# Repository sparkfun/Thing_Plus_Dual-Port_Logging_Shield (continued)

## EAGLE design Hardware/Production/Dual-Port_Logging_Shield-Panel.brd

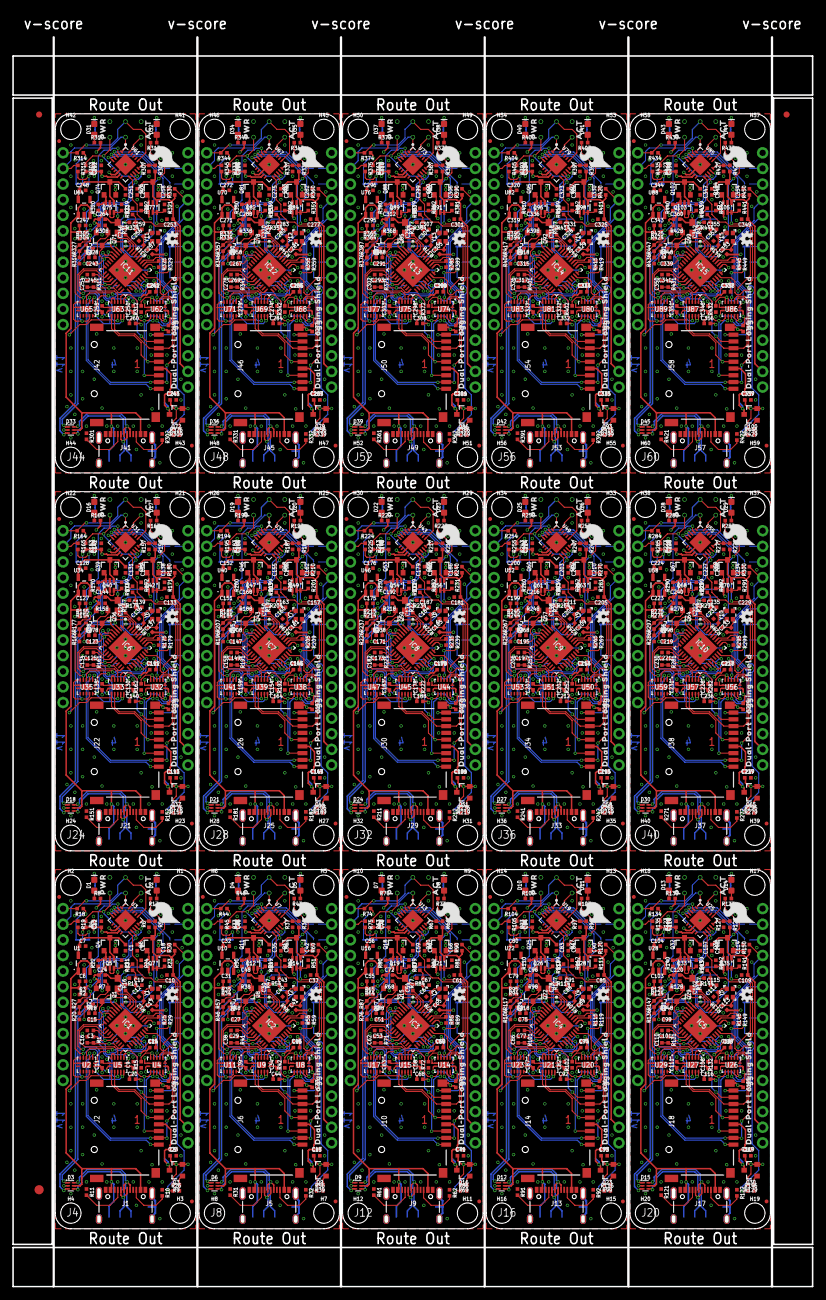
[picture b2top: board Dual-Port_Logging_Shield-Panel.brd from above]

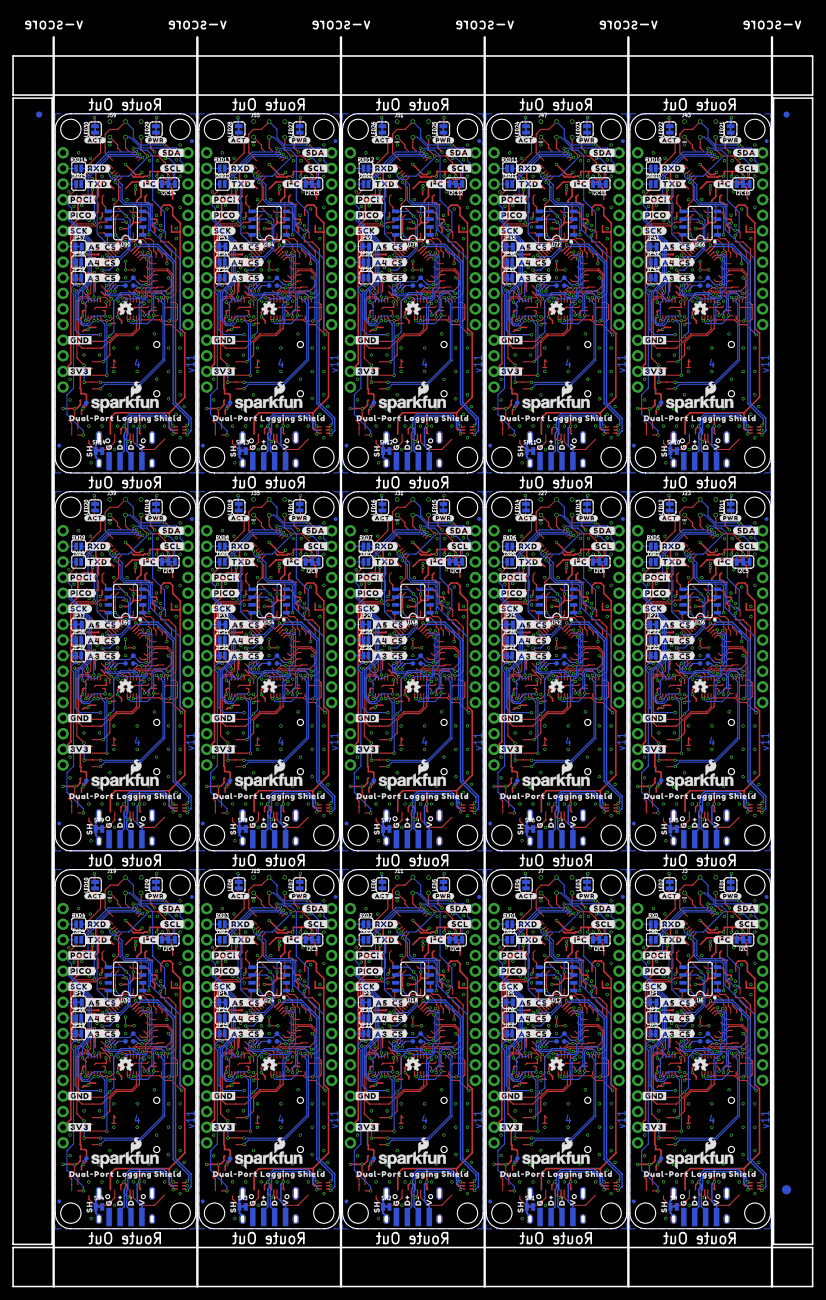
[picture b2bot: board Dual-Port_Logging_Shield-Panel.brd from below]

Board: 4 copper layers, 130.0 x 203.2 mm, 1896 parts (618 on the bottom side), 1095 nets.

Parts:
C1, C2, C5, C8, C9, C11, C13, C14, C16, C19, C25, C26, C28, C33, C34, C35, C36, C38, C39, C43, C49, C50, C52, C57, C58, C59, C60, C62, C63, C67, C73, C74, C76, C81, C82, C83, C84, C86, C87, C91, C97, C98, C100, C105, C106, C107, C108, C110, C111, C115, C121, C122, C124, C129, C130, C131, C132, C134, C135, C139, C145, C146, C148, C153, C154, C155, C156, C158, C159, C163, C169, C170, C172, C177, C178, C179, C180, C182, C183, C187, C193, C194, C196, C201, C202, C203, C204, C206, C207, C211, C217, C218, C220, C225, C226, C227, C228, C230, C231, C235, C241, C242, C244, C249, C250, C251, C252, C254, C255, C259, C265, C266, C268, C273, C274, C275, C276, C278, C279, C283, C289, C290, C292, C297, C298, C299, C300, C302, C303, C307, C313, C314, C316, C321, C322, C323, C324, C326, C327, C331, C337, C338, C340, C345, C346, C347, C348, C350, C351, C355: 0.1uF; 0402-TIGHT
C3, C4, C6, C7, C10, C15, C18, C27, C29, C30, C31, C32, C37, C42, C51, C53, C54, C55, C56, C61, C66, C75, C77, C78, C79, C80, C85, C90, C99, C101, C102, C103, C104, C109, C114, C123, C125, C126, C127, C128, C133, C138, C147, C149, C150, C151, C152, C157, C162, C171, C173, C174, C175, C176, C181, C186, C195, C197, C198, C199, C200, C205, C210, C219, C221, C222, C223, C224, C229, C234, C243, C245, C246, C247, C248, C253, C258, C267, C269, C270, C271, C272, C277, C282, C291, C293, C294, C295, C296, C301, C306, C315, C317, C318, C319, C320, C325, C330, C339, C341, C342, C343, C344, C349, C354: 2.2uF; 0402-TIGHT
C12, C17, C40, C41, C64, C65, C88, C89, C112, C113, C136, C137, C160, C161, C184, C185, C208, C209, C232, C233, C256, C257, C280, C281, C304, C305, C328, C329, C352, C353: 12pF; 0402-TIGHT
C20, C21, C22, C23, C24, C44, C45, C46, C47, C48, C68, C69, C70, C71, C72, C92, C93, C94, C95, C96, C116, C117, C118, C119, C120, C140, C141, C142, C143, C144, C164, C165, C166, C167, C168, C188, C189, C190, C191, C192, C212, C213, C214, C215, C216, C236, C237, C238, C239, C240, C260, C261, C262, C263, C264, C284, C285, C286, C287, C288, C308, C309, C310, C311, C312, C332, C333, C334, C335, C336, C356, C357, C358, C359, C360: 10uF; 0402-TIGHT
D1, D4, D7, D10, D13, D16, D19, D22, D25, D28, D31, D34, D37, D40, D43: RED; LED-0603
D2, D5, D8, D11, D14, D17, D20, D23, D26, D29, D32, D35, D38, D41, D44: Yellow; LED-0603
D3, D6, D9, D12, D15, D18, D21, D24, D27, D30, D33, D36, D39, D42, D45: PRTR5V0U2F; SOT886
E$1, E$2, E$3, E$4: FIDUCIAL-1X2
E$5, E$6: FIDUCIAL-1.5X3
FD1, FD2, FD3, FD4, FD5, FD6, FD7, FD8, FD9, FD10, FD11, FD12, FD13, FD14, FD15, FD16, FD17, FD18, FD19, FD20, FD21, FD22, FD23, FD24, FD25, FD26, FD27, FD28, FD29, FD30, FD31, FD32, FD33, FD34, FD35, FD36, FD37, FD38, FD39, FD40, FD41, FD42, FD43, FD44, FD45, FD46, FD47, FD48, FD49, FD50, FD51, FD52, FD53, FD54, FD55, FD56, FD57, FD58, FD59, FD60: FIDUCIALUFIDUCIAL; FIDUCIAL-MICRO
GPIO1, GPIO2, GPIO3, GPIO4, GPIO5, GPIO6, GPIO7, GPIO8, GPIO9, GPIO10, GPIO11, GPIO12, GPIO13, GPIO14, GPIO15: TEST-POINT3; PAD.03X.03
H1, H2, H3, H4, H5, H6, H7, H8, H9, H10, H11, H12, H13, H14, H15, H16, H17, H18, H19, H20, H21, H22, H23, H24, H25, H26, H27, H28, H29, H30, H31, H32, H33, H34, H35, H36, H37, H38, H39, H40, H41, H42, H43, H44, H45, H46, H47, H48, H49, H50, H51, H52, H53, H54, H55, H56, H57, H58, H59, H60: STAND-OFF
I2C, I2C1, I2C2, I2C3, I2C4, I2C5, I2C6, I2C7, I2C8, I2C9, I2C10, I2C11, I2C12, I2C13, I2C14: JUMPER-SMT_3_2-NC_TRACE_SILK; SMT-JUMPER_3_2-NC_TRACE_SILK
IC1, IC2, IC3, IC4, IC5, IC6, IC7, IC8, IC9, IC10, IC11, IC12, IC13, IC14, IC15: USB224X_2241_V04; 36-QFN
J1, J5, J9, J13, J17, J21, J25, J29, J33, J37, J41, J45, J49, J53, J57: USB-C-16P_4LAYER-PADS
J2, J6, J10, J14, J18, J22, J26, J30, J34, J38, J42, J46, J50, J54, J58: MICRO-SD-PUSH-PUSH-EXT-PIN; MICROSD-EXTERNALPIN
J3, J7, J11, J15, J19, J23, J27, J31, J35, J39, J43, J47, J51, J55, J59: AVR_SPI_PROG_3X2TESTPOINTS; 2X3_TEST_POINTS
J4, J8, J12, J16, J20, J24, J28, J32, J36, J40, J44, J48, J52, J56, J60: THING_PLUS
JP1, JP5, JP9, JP13, JP17, JP21, JP25, JP29, JP33, JP37, JP41, JP45, JP49, JP53, JP57: JUMPER-SMT_2_NC_TRACE_SILK; SMT-JUMPER_2_NC_TRACE_SILK
JP2, JP3, JP6, JP7, JP10, JP11, JP14, JP15, JP18, JP19, JP22, JP23, JP26, JP27, JP30, JP31, JP34, JP35, JP38, JP39, JP42, JP43, JP46, JP47, JP50, JP51, JP54, JP55, JP58, JP59: JUMPER-SMT_2_NO_SILK; SMT-JUMPER_2_NO_SILK
JP4, JP8, JP12, JP16, JP20, JP24, JP28, JP32, JP36, JP40, JP44, JP48, JP52, JP56, JP60: USB_SOLDER_PADS; USB-SOLDER-PADS
LED1, LED2, LED3, LED4, LED5, LED6, LED7, LED8, LED9, LED10, LED11, LED12, LED13, LED14, LED15, LED16, LED17, LED18, LED19, LED20, LED21, LED22, LED23, LED24, LED25, LED26, LED27, LED28, LED29, LED30: JUMPER-SMT_2_NC_TRACE_SILK; SMT-JUMPER_2_NC_TRACE_SILK
LOGO1, LOGO2, LOGO3, LOGO6, LOGO9, LOGO10, LOGO13, LOGO14, LOGO17, LOGO18, LOGO21, LOGO22, LOGO25, LOGO26, LOGO29, LOGO30, LOGO33, LOGO34, LOGO37, LOGO38, LOGO41, LOGO42, LOGO45, LOGO46, LOGO49, LOGO50, LOGO53, LOGO54, LOGO57, LOGO58: OSHW-LOGOMINI; OSHW-LOGO-MINI
LOGO4, LOGO7, LOGO11, LOGO15, LOGO19, LOGO23, LOGO27, LOGO31, LOGO35, LOGO39, LOGO43, LOGO47, LOGO51, LOGO55, LOGO59: SFE_LOGO_FLAME.2_INCH; SFE_LOGO_FLAME_.2
LOGO5, LOGO8, LOGO12, LOGO16, LOGO20, LOGO24, LOGO28, LOGO32, LOGO36, LOGO40, LOGO44, LOGO48, LOGO52, LOGO56, LOGO60: SFE_LOGO_NAME_FLAME.1_INCH; SFE_LOGO_NAME_FLAME_.1
MICROSD_VCC, MICROSD_VCC1, MICROSD_VCC2, MICROSD_VCC3, MICROSD_VCC4, MICROSD_VCC5, MICROSD_VCC6, MICROSD_VCC7, MICROSD_VCC8, MICROSD_VCC9, MICROSD_VCC10, MICROSD_VCC11, MICROSD_VCC12, MICROSD_VCC13, MICROSD_VCC14: TEST-POINT3; PAD.03X.03
Q1, Q3, Q4, Q6, Q8, Q9, Q11, Q13, Q15, Q16, Q18, Q20, Q22, Q23, Q25, Q27, Q29, Q30, Q32, Q34, Q36, Q37, Q39, Q41, Q43, Q44, Q46, Q48, Q50, Q51, Q53, Q55, Q57, Q58, Q60, Q62, Q64, Q65, Q67, Q69, Q71, Q72, Q74, Q76, Q78, Q79, Q81, Q83, Q85, Q86, Q88, Q90, Q92, Q93, Q95, Q97, Q99, Q100, Q102, Q104: 20V/4.2A/52mΩ/1.4W; SOT23-3
Q2, Q10, Q17, Q24, Q31, Q38, Q45, Q52, Q59, Q66, Q73, Q80, Q87, Q94, Q101: 20V/0.2A/8MHz/1.2Ω/1Vth; SOT-416FL
Q5, Q7, Q12, Q14, Q19, Q21, Q26, Q28, Q33, Q35, Q40, Q42, Q47, Q49, Q54, Q56, Q61, Q63, Q68, Q70, Q75, Q77, Q82, Q84, Q89, Q91, Q96, Q98, Q103, Q105: SOT363_PHILIPS
R1, R5, R6, R7, R9, R15, R20, R21, R23, R36, R37, R38, R39, R41, R42, R46, R49, R51, R66, R67, R68, R69, R71, R72, R76, R79, R81, R96, R97, R98, R99, R101, R102, R106, R109, R111, R126, R127, R128, R129, R131, R132, R136, R139, R141, R156, R157, R158, R159, R161, R162, R166, R169, R171, R186, R187, R188, R189, R191, R192, R196, R199, R201, R216, R217, R218, R219, R221, R222, R226, R229, R231, R246, R247, R248, R249, R251, R252, R256, R259, R261, R276, R277, R278, R279, R281, R282, R286, R289, R291, R306, R307, R308, R309, R311, R312, R316, R319, R321, R336, R337, R338, R339, R341, R342, R346, R349, R351, R366, R367, R368, R369, R371, R372, R376, R379, R381, R396, R397, R398, R399, R401, R402, R406, R409, R411, R426, R427, R428, R429, R431, R432, R436, R439, R441: 100k; 0402-TIGHT
R2, R3, R4, R13, R14, R25, R29, R30, R33, R34, R35, R53, R54, R55, R59, R60, R63, R64, R65, R83, R84, R85, R89, R90, R93, R94, R95, R113, R114, R115, R119, R120, R123, R124, R125, R143, R144, R145, R149, R150, R153, R154, R155, R173, R174, R175, R179, R180, R183, R184, R185, R203, R204, R205, R209, R210, R213, R214, R215, R233, R234, R235, R239, R240, R243, R244, R245, R263, R264, R265, R269, R270, R273, R274, R275, R293, R294, R295, R299, R300, R303, R304, R305, R323, R324, R325, R329, R330, R333, R334, R335, R353, R354, R355, R359, R360, R363, R364, R365, R383, R384, R385, R389, R390, R393, R394, R395, R413, R414, R415, R419, R420, R423, R424, R425, R443, R444, R445, R449, R450: 10k; 0402-TIGHT
R8, R17, R40, R43, R70, R73, R100, R103, R130, R133, R160, R163, R190, R193, R220, R223, R250, R253, R280, R283, R310, R313, R340, R343, R370, R373, R400, R403, R430, R433: 1k; 0402-TIGHT
R10, R11, R31, R32, R61, R62, R91, R92, R121, R122, R151, R152, R181, R182, R211, R212, R241, R242, R271, R272, R301, R302, R331, R332, R361, R362, R391, R392, R421, R422: 5.1k; 0402-TIGHT
R12, R22, R24, R48, R50, R52, R78, R80, R82, R108, R110, R112, R138, R140, R142, R168, R170, R172, R198, R200, R202, R228, R230, R232, R258, R260, R262, R288, R290, R292, R318, R320, R322, R348, R350, R352, R378, R380, R382, R408, R410, R412, R438, R440, R442: 1M; 0402-TIGHT
R16, R47, R77, R107, R137, R167, R197, R227, R257, R287, R317, R347, R377, R407, R437: 12k; 0603
R18, R19, R44, R45, R74, R75, R104, R105, R134, R135, R164, R165, R194, R195, R224, R225, R254, R255, R284, R285, R314, R315, R344, R345, R374, R375, R404, R405, R434, R435: 2.2k; 0402-TIGHT
R26, R27, R28, R56, R57, R58, R86, R87, R88, R116, R117, R118, R146, R147, R148, R176, R177, R178, R206, R207, R208, R236, R237, R238, R266, R267, R268, R296, R297, R298, R326, R327, R328, R356, R357, R358, R386, R387, R388, R416, R417, R418, R446, R447, R448: 100; 0402-TIGHT
RXD, RXD1, RXD2, RXD3, RXD4, RXD5, RXD6, RXD7, RXD8, RXD9, RXD10, RXD11, RXD12, RXD13, RXD14: JUMPER-SMT_2_NO_SILK; SMT-JUMPER_2_NO_SILK
SDIO_!RESET!, SDIO_!RESET!1, SDIO_!RESET!2, SDIO_!RESET!3, SDIO_!RESET!4, SDIO_!RESET!5, SDIO_!RESET!6, SDIO_!RESET!7, SDIO_!RESET!8, SDIO_!RESET!9, SDIO_!RESET!10, SDIO_!RESET!11, SDIO_!RESET!12, SDIO_!RESET!13, SDIO_!RESET!14: TEST-POINT3; PAD.03X.03
SDIO_VDD, SDIO_VDD1, SDIO_VDD2, SDIO_VDD3, SDIO_VDD4, SDIO_VDD5, SDIO_VDD6, SDIO_VDD7, SDIO_VDD8, SDIO_VDD9, SDIO_VDD10, SDIO_VDD11, SDIO_VDD12, SDIO_VDD13, SDIO_VDD14: TEST-POINT3; PAD.03X.03
SH, SH1, SH2, SH3, SH4, SH5, SH6, SH7, SH8, SH9, SH10, SH11, SH12, SH13, SH14: JUMPER-SMT_2_NC_TRACE_NO-SILK; SMT-JUMPER_2_NC_TRACE_NO-SILK
TXD, TXD1, TXD2, TXD3, TXD4, TXD5, TXD6, TXD7, TXD8, TXD9, TXD10, TXD11, TXD12, TXD13, TXD14: JUMPER-SMT_2_NO_SILK; SMT-JUMPER_2_NO_SILK
U1, U10, U16, U22, U28, U34, U40, U46, U52, U58, U64, U70, U76, U82, U88: 3.3V; SOT23-5
U2, U4, U5, U8, U9, U11, U14, U15, U17, U20, U21, U23, U26, U27, U29, U32, U33, U35, U38, U39, U41, U44, U45, U47, U50, U51, U53, U56, U57, U59, U62, U63, U65, U68, U69, U71, U74, U75, U77, U80, U81, U83, U86, U87, U89: 74HC4066_QUAD_BILATERAL_SWITCH_QFN; 14-QFN
U3, U7, U13, U19, U25, U31, U37, U43, U49, U55, U61, U67, U73, U79, U85: ATTINY841-ARDUINO_QFN20M1; QFN20_20M1
U6, U12, U18, U24, U30, U36, U42, U48, U54, U60, U66, U72, U78, U84, U90: 24C04; SO08
U$1, U$32, U$56, U$80, U$104, U$128, U$152, U$176, U$200, U$224, U$248, U$272, U$296, U$320, U$344: #SDA#0
U$2, U$33, U$57, U$81, U$105, U$129, U$153, U$177, U$201, U$225, U$249, U$273, U$297, U$321, U$345: #SCL#1
U$3, U$36, U$60, U$84, U$108, U$132, U$156, U$180, U$204, U$228, U$252, U$276, U$300, U$324, U$348: #POCI#0
U$4, U$37, U$61, U$85, U$109, U$133, U$157, U$181, U$205, U$229, U$253, U$277, U$301, U$325, U$349: #PICO#1
U$5, U$38, U$62, U$86, U$110, U$134, U$158, U$182, U$206, U$230, U$254, U$278, U$302, U$326, U$350: #SCK#2
U$6, U$14, U$30, U$31, U$54, U$55, U$78, U$79, U$102, U$103, U$126, U$127, U$150, U$151, U$174, U$175, U$198, U$199, U$222, U$223, U$246, U$247, U$270, U$271, U$294, U$295, U$318, U$319, U$342, U$343: DUAL#PORT_LOGGING_SHIELD0
U$7, U$42, U$66, U$90, U$114, U$138, U$162, U$186, U$210, U$234, U$258, U$282, U$306, U$330, U$354: #GND#0
U$8, U$43, U$67, U$91, U$115, U$139, U$163, U$187, U$211, U$235, U$259, U$283, U$307, U$331, U$355: #3V3#1
U$9, U$34, U$58, U$82, U$106, U$130, U$154, U$178, U$202, U$226, U$250, U$274, U$298, U$322, U$346: #RXD#0
U$10, U$35, U$59, U$83, U$107, U$131, U$155, U$179, U$203, U$227, U$251, U$275, U$299, U$323, U$347: #TXD#1
U$11, U$24, U$49, U$73, U$97, U$121, U$145, U$169, U$193, U$217, U$241, U$265, U$289, U$313, U$337: PWR0
U$12, U$26, U$50, U$74, U$98, U$122, U$146, U$170, U$194, U$218, U$242, U$266, U$290, U$314, U$338: ACT0
U$13, U$27, U$51, U$75, U$99, U$123, U$147, U$171, U$195, U$219, U$243, U$267, U$291, U$315, U$339: #I�C#0
U$15, U$28, U$52, U$76, U$100, U$124, U$148, U$172, U$196, U$220, U$244, U$268, U$292, U$316, U$340: #PWR#0
U$16, U$29, U$53, U$77, U$101, U$125, U$149, U$173, U$197, U$221, U$245, U$269, U$293, U$317, U$341: #ACT#0
U$17, U$39, U$63, U$87, U$111, U$135, U$159, U$183, U$207, U$231, U$255, U$279, U$303, U$327, U$351: #A5__#CS##0
U$18, U$40, U$64, U$88, U$112, U$136, U$160, U$184, U$208, U$232, U$256, U$280, U$304, U$328, U$352: #A4__#CS##6
U$19, U$41, U$65, U$89, U$113, U$137, U$161, U$185, U$209, U$233, U$257, U$281, U$305, U$329, U$353: #A3__#CS##6
U$20, U$48, U$72, U$96, U$120, U$144, U$168, U$192, U$216, U$240, U$264, U$288, U$312, U$336, U$360: SH0
U$21, U$44, U$68, U$92, U$116, U$140, U$164, U$188, U$212, U$236, U$260, U$284, U$308, U$332, U$356: G0
U$22, U$45, U$69, U$93, U$117, U$141, U$165, U$189, U$213, U$237, U$261, U$285, U$309, U$333, U$357: V0
U$23, U$46, U$70, U$94, U$118, U$142, U$166, U$190, U$214, U$238, U$262, U$286, U$310, U$334, U$358: D#0
U$25, U$47, U$71, U$95, U$119, U$143, U$167, U$191, U$215, U$239, U$263, U$287, U$311, U$335, U$359: D#1
Y1, Y2, Y3, Y4, Y5, Y6, Y7, Y8, Y9, Y10, Y11, Y12, Y13, Y14, Y15: 24MHz; CRYSTAL-SMD-2.0X1.6MM

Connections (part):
3.3V: C2.1, C10.1, J4.27, Q6.3, Q7.1, R5.2, R30.1
3.3V1: C36.1, C37.1, J8.27, Q13.3, Q14.1, R36.2, R60.1
3.3V2: C60.1, C61.1, J12.27, Q20.3, Q21.1, R66.2, R90.1
3.3V3: C84.1, C85.1, J16.27, Q27.3, Q28.1, R96.2, R120.1
3.3V4: C108.1, C109.1, J20.27, Q34.3, Q35.1, R126.2, R150.1
3.3V5: C132.1, C133.1, J24.27, Q41.3, Q42.1, R156.2, R180.1
3.3V6: C156.1, C157.1, J28.27, Q48.3, Q49.1, R186.2, R210.1
3.3V7: C180.1, C181.1, J32.27, Q55.3, Q56.1, R216.2, R240.1
3.3V8: C204.1, C205.1, J36.27, Q62.3, Q63.1, R246.2, R270.1
3.3V9: C228.1, C229.1, J40.27, Q69.3, Q70.1, R276.2, R300.1
3.3V10: C252.1, C253.1, J44.27, Q76.3, Q77.1, R306.2, R330.1
3.3V11: C276.1, C277.1, J48.27, Q83.3, Q84.1, R336.2, R360.1
3.3V12: C300.1, C301.1, J52.27, Q90.3, Q91.1, R366.2, R390.1
3.3V13: C324.1, C325.1, J56.27, Q97.3, Q98.1, R396.2, R420.1
3.3V14: C348.1, C349.1, J60.27, Q104.3, Q105.1, R426.2, R450.1
3V3_DIV_1: R36.1, R37.2, U7.15
3V3_DIV_2: R5.1, R6.2, U3.15
3V3_DIV_3: R66.1, R67.2, U13.15
3V3_DIV_4: R96.1, R97.2, U19.15
3V3_DIV_5: R126.1, R127.2, U25.15
3V3_DIV_6: R156.1, R157.2, U31.15
3V3_DIV_7: R186.1, R187.2, U37.15
3V3_DIV_8: R216.1, R217.2, U43.15
3V3_DIV_9: R246.1, R247.2, U49.15
3V3_DIV_10: R276.1, R277.2, U55.15
3V3_DIV_11: R306.1, R307.2, U61.15
3V3_DIV_12: R336.1, R337.2, U67.15
3V3_DIV_13: R366.1, R367.2, U73.15
3V3_DIV_14: R396.1, R397.2, U79.15
3V3_DIV_15: R426.1, R427.2, U85.15
!CS!: JP1.2, JP2.2, JP3.2, U4.4
!CS!1: JP5.2, JP6.2, JP7.2, U8.4
!CS!2: JP9.2, JP10.2, JP11.2, U14.4
!CS!3: JP13.2, JP14.2, JP15.2, U20.4
!CS!4: JP17.2, JP18.2, JP19.2, U26.4
!CS!5: JP21.2, JP22.2, JP23.2, U32.4
!CS!6: JP25.2, JP26.2, JP27.2, U38.4
!CS!7: JP29.2, JP30.2, JP31.2, U44.4
!CS!8: JP33.2, JP34.2, JP35.2, U50.4
!CS!9: JP37.2, JP38.2, JP39.2, U56.4
!CS!10: JP41.2, JP42.2, JP43.2, U62.4
!CS!11: JP45.2, JP46.2, JP47.2, U68.4
!CS!12: JP49.2, JP50.2, JP51.2, U74.4
!CS!13: JP53.2, JP54.2, JP55.2, U80.4
!CS!14: JP57.2, JP58.2, JP59.2, U86.4
!RESET!: J3.5, R4.1, U3.13
!RESET!1: J7.5, R33.1, U7.13
!RESET!2: J11.5, R63.1, U13.13
!RESET!3: J15.5, R93.1, U19.13
!RESET!4: J19.5, R123.1, U25.13
!RESET!5: J23.5, R153.1, U31.13
!RESET!6: J27.5, R183.1, U37.13
!RESET!7: J31.5, R213.1, U43.13
!RESET!8: J35.5, R243.1, U49.13
!RESET!9: J39.5, R273.1, U55.13
!RESET!10: J43.5, R303.1, U61.13
!RESET!11: J47.5, R333.1, U67.13
!RESET!12: J51.5, R363.1, U73.13
!RESET!13: J55.5, R393.1, U79.13
!RESET!14: J59.5, R423.1, U85.13
ACTIVITY: IC1.1, R17.2
ACTIVITY1: IC2.1, R43.2
ACTIVITY2: IC3.1, R73.2
ACTIVITY3: IC4.1, R103.2
ACTIVITY4: IC5.1, R133.2
ACTIVITY5: IC6.1, R163.2
ACTIVITY6: IC7.1, R193.2
ACTIVITY7: IC8.1, R223.2
ACTIVITY8: IC9.1, R253.2
ACTIVITY9: IC10.1, R283.2
ACTIVITY10: IC11.1, R313.2
ACTIVITY11: IC12.1, R343.2
ACTIVITY12: IC13.1, R373.2
ACTIVITY13: IC14.1, R403.2
ACTIVITY14: IC15.1, R433.2
AT_POCI: J3.1, U3.20
AT_POCI1: J7.1, U7.20
AT_POCI2: J11.1, U13.20
AT_POCI3: J15.1, U19.20
AT_POCI4: J19.1, U25.20
AT_POCI5: J23.1, U31.20
AT_POCI6: J27.1, U37.20
AT_POCI7: J31.1, U43.20
AT_POCI8: J35.1, U49.20
AT_POCI9: J39.1, U55.20
AT_POCI10: J43.1, U61.20
AT_POCI11: J47.1, U67.20
AT_POCI12: J51.1, U73.20
AT_POCI13: J55.1, U79.20
AT_POCI14: J59.1, U85.20
D+: D3.1, IC1.2
D+1: D6.1, IC2.2
D+2: D9.1, IC3.2
D+3: D12.1, IC4.2
D+4: D15.1, IC5.2
D+5: D18.1, IC6.2
D+6: D21.1, IC7.2
D+7: D24.1, IC8.2
D+8: D27.1, IC9.2
D+9: D30.1, IC10.2
D+10: D33.1, IC11.2
D+11: D36.1, IC12.2
D+12: D39.1, IC13.2
D+13: D42.1, IC14.2
D+14: D45.1, IC15.2
D+_IN: D3.6, J1.A6, J1.B6, JP4.D+
D+_IN1: D6.6, J5.A6, J5.B6, JP8.D+
D+_IN2: D9.6, J9.A6, J9.B6, JP12.D+
D+_IN3: D12.6, J13.A6, J13.B6, JP16.D+
D+_IN4: D15.6, J17.A6, J17.B6, JP20.D+
D+_IN5: D18.6, J21.A6, J21.B6, JP24.D+
D+_IN6: D21.6, J25.A6, J25.B6, JP28.D+
D+_IN7: D24.6, J29.A6, J29.B6, JP32.D+
D+_IN8: D27.6, J33.A6, J33.B6, JP36.D+
D+_IN9: D30.6, J37.A6, J37.B6, JP40.D+
D+_IN10: D33.6, J41.A6, J41.B6, JP44.D+
D+_IN11: D36.6, J45.A6, J45.B6, JP48.D+
D+_IN12: D39.6, J49.A6, J49.B6, JP52.D+
D+_IN13: D42.6, J53.A6, J53.B6, JP56.D+
D+_IN14: D45.6, J57.A6, J57.B6, JP60.D+
D-: D3.3, IC1.3
D-1: D6.3, IC2.3
D-2: D9.3, IC3.3
D-3: D12.3, IC4.3
D-4: D15.3, IC5.3
D-5: D18.3, IC6.3
D-6: D21.3, IC7.3
D-7: D24.3, IC8.3
D-8: D27.3, IC9.3
D-9: D30.3, IC10.3
D-10: D33.3, IC11.3
D-11: D36.3, IC12.3
D-12: D39.3, IC13.3
D-13: D42.3, IC14.3
D-14: D45.3, IC15.3
D-_IN: D3.4, J1.A7, J1.B7, JP4.D-
D-_IN1: D6.4, J5.A7, J5.B7, JP8.D-
D-_IN2: D9.4, J9.A7, J9.B7, JP12.D-
D-_IN3: D12.4, J13.A7, J13.B7, JP16.D-
D-_IN4: D15.4, J17.A7, J17.B7, JP20.D-
D-_IN5: D18.4, J21.A7, J21.B7, JP24.D-
D-_IN6: D21.4, J25.A7, J25.B7, JP28.D-
D-_IN7: D24.4, J29.A7, J29.B7, JP32.D-
D-_IN8: D27.4, J33.A7, J33.B7, JP36.D-
D-_IN9: D30.4, J37.A7, J37.B7, JP40.D-
D-_IN10: D33.4, J41.A7, J41.B7, JP44.D-
D-_IN11: D36.4, J45.A7, J45.B7, JP48.D-
D-_IN12: D39.4, J49.A7, J49.B7, JP52.D-
D-_IN13: D42.4, J53.A7, J53.B7, JP56.D-
D-_IN14: D45.4, J57.A7, J57.B7, JP60.D-
GND: C1.2, C2.2, C3.2, C4.2, C5.2, C6.2, C7.2, C8.2, C9.2, C10.2, C11.2, C12.1, C13.2, C14.2, C15.2, C16.2, C17.1, C18.2, C19.2, C20.2, C21.2, C22.2, C23.2, C24.2, D3.2, IC1.28, IC1.EPAD, J1.GND, J1.GND2, J2.6, J2.10, J2.11, J2.12, J2.13, J3.6, J4.25, JP4.GND, LED1.1, LED2.1, Q2.2, R3.1, R6.1, R10.1, R11.1, R15.1, R16.1, R20.1, R21.1, R22.1, R23.1, R24.1, R25.2, R29.2, SH.2, U1.2, U2.6, U2.7, U2.12, U2.EPAD, U3.8, U3.PAD, U4.7, U4.EPAD, U5.7, U5.EPAD, U6.1, U6.2, U6.3, U6.4, U6.7
GND1: C25.2, C26.2, C27.2, C28.2, C29.2, C30.2, C31.2, C32.2, C33.2, C34.2, C35.2, C36.2, C37.2, C38.2, C39.2, C40.1, C41.1, C42.2, C43.2, C44.2, C45.2, C46.2, C47.2, C48.2, D6.2, IC2.28, IC2.EPAD, J5.GND, J5.GND2, J6.6, J6.10, J6.11, J6.12, J6.13, J7.6, J8.25, JP8.GND, LED3.1, LED4.1, Q10.2, R31.1, R32.1, R35.1, R37.1, R42.1, R46.1, R47.1, R49.1, R50.1, R51.1, R52.1, R55.2, R59.2, SH1.2, U7.8, U7.PAD, U8.7, U8.EPAD, U9.7, U9.EPAD, U10.2, U11.6, U11.7, U11.12, U11.EPAD, U12.1, U12.2, U12.3, U12.4, U12.7
GND2: C49.2, C50.2, C51.2, C52.2, C53.2, C54.2, C55.2, C56.2, C57.2, C58.2, C59.2, C60.2, C61.2, C62.2, C63.2, C64.1, C65.1, C66.2, C67.2, C68.2, C69.2, C70.2, C71.2, C72.2, D9.2, IC3.28, IC3.EPAD, J9.GND, J9.GND2, J10.6, J10.10, J10.11, J10.12, J10.13, J11.6, J12.25, JP12.GND, LED5.1, LED6.1, Q17.2, R61.1, R62.1, R65.1, R67.1, R72.1, R76.1, R77.1, R79.1, R80.1, R81.1, R82.1, R85.2, R89.2, SH2.2, U13.8, U13.PAD, U14.7, U14.EPAD, U15.7, U15.EPAD, U16.2, U17.6, U17.7, U17.12, U17.EPAD, U18.1, U18.2, U18.3, U18.4, U18.7
GND3: C73.2, C74.2, C75.2, C76.2, C77.2, C78.2, C79.2, C80.2, C81.2, C82.2, C83.2, C84.2, C85.2, C86.2, C87.2, C88.1, C89.1, C90.2, C91.2, C92.2, C93.2, C94.2, C95.2, C96.2, D12.2, IC4.28, IC4.EPAD, J13.GND, J13.GND2, J14.6, J14.10, J14.11, J14.12, J14.13, J15.6, J16.25, JP16.GND, LED7.1, LED8.1, Q24.2, R91.1, R92.1, R95.1, R97.1, R102.1, R106.1, R107.1, R109.1, R110.1, R111.1, R112.1, R115.2, R119.2, SH3.2, U19.8, U19.PAD, U20.7, U20.EPAD, U21.7, U21.EPAD, U22.2, U23.6, U23.7, U23.12, U23.EPAD, U24.1, U24.2, U24.3, U24.4, U24.7
GND4: C97.2, C98.2, C99.2, C100.2, C101.2, C102.2, C103.2, C104.2, C105.2, C106.2, C107.2, C108.2, C109.2, C110.2, C111.2, C112.1, C113.1, C114.2, C115.2, C116.2, C117.2, C118.2, C119.2, C120.2, D15.2, IC5.28, IC5.EPAD, J17.GND, J17.GND2, J18.6, J18.10, J18.11, J18.12, J18.13, J19.6, J20.25, JP20.GND, LED9.1, LED10.1, Q31.2, R121.1, R122.1, R125.1, R127.1, R132.1, R136.1, R137.1, R139.1, R140.1, R141.1, R142.1, R145.2, R149.2, SH4.2, U25.8, U25.PAD, U26.7, U26.EPAD, U27.7, U27.EPAD, U28.2, U29.6, U29.7, U29.12, U29.EPAD, U30.1, U30.2, U30.3, U30.4, U30.7
GND5: C121.2, C122.2, C123.2, C124.2, C125.2, C126.2, C127.2, C128.2, C129.2, C130.2, C131.2, C132.2, C133.2, C134.2, C135.2, C136.1, C137.1, C138.2, C139.2, C140.2, C141.2, C142.2, C143.2, C144.2, D18.2, IC6.28, IC6.EPAD, J21.GND, J21.GND2, J22.6, J22.10, J22.11, J22.12, J22.13, J23.6, J24.25, JP24.GND, LED11.1, LED12.1, Q38.2, R151.1, R152.1, R155.1, R157.1, R162.1, R166.1, R167.1, R169.1, R170.1, R171.1, R172.1, R175.2, R179.2, SH5.2, U31.8, U31.PAD, U32.7, U32.EPAD, U33.7, U33.EPAD, U34.2, U35.6, U35.7, U35.12, U35.EPAD, U36.1, U36.2, U36.3, U36.4, U36.7
GND6: C145.2, C146.2, C147.2, C148.2, C149.2, C150.2, C151.2, C152.2, C153.2, C154.2, C155.2, C156.2, C157.2, C158.2, C159.2, C160.1, C161.1, C162.2, C163.2, C164.2, C165.2, C166.2, C167.2, C168.2, D21.2, IC7.28, IC7.EPAD, J25.GND, J25.GND2, J26.6, J26.10, J26.11, J26.12, J26.13, J27.6, J28.25, JP28.GND, LED13.1, LED14.1, Q45.2, R181.1, R182.1, R185.1, R187.1, R192.1, R196.1, R197.1, R199.1, R200.1, R201.1, R202.1, R205.2, R209.2, SH6.2, U37.8, U37.PAD, U38.7, U38.EPAD, U39.7, U39.EPAD, U40.2, U41.6, U41.7, U41.12, U41.EPAD, U42.1, U42.2, U42.3, U42.4, U42.7
GND7: C169.2, C170.2, C171.2, C172.2, C173.2, C174.2, C175.2, C176.2, C177.2, C178.2, C179.2, C180.2, C181.2, C182.2, C183.2, C184.1, C185.1, C186.2, C187.2, C188.2, C189.2, C190.2, C191.2, C192.2, D24.2, IC8.28, IC8.EPAD, J29.GND, J29.GND2, J30.6, J30.10, J30.11, J30.12, J30.13, J31.6, J32.25, JP32.GND, LED15.1, LED16.1, Q52.2, R211.1, R212.1, R215.1, R217.1, R222.1, R226.1, R227.1, R229.1, R230.1, R231.1, R232.1, R235.2, R239.2, SH7.2, U43.8, U43.PAD, U44.7, U44.EPAD, U45.7, U45.EPAD, U46.2, U47.6, U47.7, U47.12, U47.EPAD, U48.1, U48.2, U48.3, U48.4, U48.7
GND8: C193.2, C194.2, C195.2, C196.2, C197.2, C198.2, C199.2, C200.2, C201.2, C202.2, C203.2, C204.2, C205.2, C206.2, C207.2, C208.1, C209.1, C210.2, C211.2, C212.2, C213.2, C214.2, C215.2, C216.2, D27.2, IC9.28, IC9.EPAD, J33.GND, J33.GND2, J34.6, J34.10, J34.11, J34.12, J34.13, J35.6, J36.25, JP36.GND, LED17.1, LED18.1, Q59.2, R241.1, R242.1, R245.1, R247.1, R252.1, R256.1, R257.1, R259.1, R260.1, R261.1, R262.1, R265.2, R269.2, SH8.2, U49.8, U49.PAD, U50.7, U50.EPAD, U51.7, U51.EPAD, U52.2, U53.6, U53.7, U53.12, U53.EPAD, U54.1, U54.2, U54.3, U54.4, U54.7
GND9: C217.2, C218.2, C219.2, C220.2, C221.2, C222.2, C223.2, C224.2, C225.2, C226.2, C227.2, C228.2, C229.2, C230.2, C231.2, C232.1, C233.1, C234.2, C235.2, C236.2, C237.2, C238.2, C239.2, C240.2, D30.2, IC10.28, IC10.EPAD, J37.GND, J37.GND2, J38.6, J38.10, J38.11, J38.12, J38.13, J39.6, J40.25, JP40.GND, LED19.1, LED20.1, Q66.2, R271.1, R272.1, R275.1, R277.1, R282.1, R286.1, R287.1, R289.1, R290.1, R291.1, R292.1, R295.2, R299.2, SH9.2, U55.8, U55.PAD, U56.7, U56.EPAD, U57.7, U57.EPAD, U58.2, U59.6, U59.7, U59.12, U59.EPAD, U60.1, U60.2, U60.3, U60.4, U60.7
GND10: C241.2, C242.2, C243.2, C244.2, C245.2, C246.2, C247.2, C248.2, C249.2, C250.2, C251.2, C252.2, C253.2, C254.2, C255.2, C256.1, C257.1, C258.2, C259.2, C260.2, C261.2, C262.2, C263.2, C264.2, D33.2, IC11.28, IC11.EPAD, J41.GND, J41.GND2, J42.6, J42.10, J42.11, J42.12, J42.13, J43.6, J44.25, JP44.GND, LED21.1, LED22.1, Q73.2, R301.1, R302.1, R305.1, R307.1, R312.1, R316.1, R317.1, R319.1, R320.1, R321.1, R322.1, R325.2, R329.2, SH10.2, U61.8, U61.PAD, U62.7, U62.EPAD, U63.7, U63.EPAD, U64.2, U65.6, U65.7, U65.12, U65.EPAD, U66.1, U66.2, U66.3, U66.4, U66.7
GND11: C265.2, C266.2, C267.2, C268.2, C269.2, C270.2, C271.2, C272.2, C273.2, C274.2, C275.2, C276.2, C277.2, C278.2, C279.2, C280.1, C281.1, C282.2, C283.2, C284.2, C285.2, C286.2, C287.2, C288.2, D36.2, IC12.28, IC12.EPAD, J45.GND, J45.GND2, J46.6, J46.10, J46.11, J46.12, J46.13, J47.6, J48.25, JP48.GND, LED23.1, LED24.1, Q80.2, R331.1, R332.1, R335.1, R337.1, R342.1, R346.1, R347.1, R349.1, R350.1, R351.1, R352.1, R355.2, R359.2, SH11.2, U67.8, U67.PAD, U68.7, U68.EPAD, U69.7, U69.EPAD, U70.2, U71.6, U71.7, U71.12, U71.EPAD, U72.1, U72.2, U72.3, U72.4, U72.7
GND12: C289.2, C290.2, C291.2, C292.2, C293.2, C294.2, C295.2, C296.2, C297.2, C298.2, C299.2, C300.2, C301.2, C302.2, C303.2, C304.1, C305.1, C306.2, C307.2, C308.2, C309.2, C310.2, C311.2, C312.2, D39.2, IC13.28, IC13.EPAD, J49.GND, J49.GND2, J50.6, J50.10, J50.11, J50.12, J50.13, J51.6, J52.25, JP52.GND, LED25.1, LED26.1, Q87.2, R361.1, R362.1, R365.1, R367.1, R372.1, R376.1, R377.1, R379.1, R380.1, R381.1, R382.1, R385.2, R389.2, SH12.2, U73.8, U73.PAD, U74.7, U74.EPAD, U75.7, U75.EPAD, U76.2, U77.6, U77.7, U77.12, U77.EPAD, U78.1, U78.2, U78.3, U78.4, U78.7
GND13: C313.2, C314.2, C315.2, C316.2, C317.2, C318.2, C319.2, C320.2, C321.2, C322.2, C323.2, C324.2, C325.2, C326.2, C327.2, C328.1, C329.1, C330.2, C331.2, C332.2, C333.2, C334.2, C335.2, C336.2, D42.2, IC14.28, IC14.EPAD, J53.GND, J53.GND2, J54.6, J54.10, J54.11, J54.12, J54.13, J55.6, J56.25, JP56.GND, LED27.1, LED28.1, Q94.2, R391.1, R392.1, R395.1, R397.1, R402.1, R406.1, R407.1, R409.1, R410.1, R411.1, R412.1, R415.2, R419.2, SH13.2, U79.8, U79.PAD, U80.7, U80.EPAD, U81.7, U81.EPAD, U82.2, U83.6, U83.7, U83.12, U83.EPAD, U84.1, U84.2, U84.3, U84.4, U84.7
GND14: C337.2, C338.2, C339.2, C340.2, C341.2, C342.2, C343.2, C344.2, C345.2, C346.2, C347.2, C348.2, C349.2, C350.2, C351.2, C352.1, C353.1, C354.2, C355.2, C356.2, C357.2, C358.2, C359.2, C360.2, D45.2, IC15.28, IC15.EPAD, J57.GND, J57.GND2, J58.6, J58.10, J58.11, J58.12, J58.13, J59.6, J60.25, JP60.GND, LED29.1, LED30.1, Q101.2, R421.1, R422.1, R425.1, R427.1, R432.1, R436.1, R437.1, R439.1, R440.1, R441.1, R442.1, R445.2, R449.2, SH14.2, U85.8, U85.PAD, U86.7, U86.EPAD, U87.7, U87.EPAD, U88.2, U89.6, U89.7, U89.12, U89.EPAD, U90.1, U90.2, U90.3, U90.4, U90.7
GPIO1: IC2.27, R53.2, U12.5
GPIO2: IC1.27, R13.2, U6.5
GPIO3: IC2.29, R55.1
GPIO4: IC1.29, R25.1
GPIO5: IC2.31, R54.2, U12.6
GPIO6: GPIO1.1, IC2.21
GPIO7: IC1.31, R14.2, U6.6
GPIO8: IC3.27, R83.2, U18.5
GPIO9: IC3.29, R85.1
GPIO10: GPIO10.1, IC1.21
GPIO11: IC3.31, R84.2, U18.6
GPIO12: GPIO2.1, IC3.21
GPIO13: IC4.27, R113.2, U24.5
GPIO14: IC4.29, R115.1
GPIO15: IC4.31, R114.2, U24.6
GPIO16: GPIO3.1, IC4.21
GPIO17: IC5.27, R143.2, U30.5
GPIO18: IC5.29, R145.1
GPIO19: IC5.31, R144.2, U30.6
GPIO20: GPIO4.1, IC5.21
GPIO21: IC6.27, R173.2, U36.5
GPIO22: IC6.29, R175.1
GPIO23: IC6.31, R174.2, U36.6
GPIO24: GPIO5.1, IC6.21
GPIO25: IC7.27, R203.2, U42.5
GPIO26: IC7.29, R205.1
GPIO27: IC7.31, R204.2, U42.6
GPIO28: GPIO6.1, IC7.21
GPIO29: IC8.27, R233.2, U48.5
GPIO30: IC8.29, R235.1
GPIO31: IC8.31, R234.2, U48.6
GPIO32: GPIO7.1, IC8.21
GPIO33: IC9.27, R263.2, U54.5
GPIO34: IC9.29, R265.1
GPIO35: IC9.31, R264.2, U54.6
GPIO36: GPIO8.1, IC9.21
GPIO37: IC10.27, R293.2, U60.5
GPIO38: IC10.29, R295.1
GPIO39: IC10.31, R294.2, U60.6
GPIO40: GPIO9.1, IC10.21
GPIO41: IC11.27, R323.2, U66.5
GPIO42: IC11.29, R325.1
GPIO43: IC11.31, R324.2, U66.6
GPIO44: GPIO11.1, IC11.21
GPIO45: IC12.27, R353.2, U72.5
GPIO46: IC12.29, R355.1
GPIO47: IC12.31, R354.2, U72.6
GPIO48: GPIO12.1, IC12.21
GPIO49: IC13.27, R383.2, U78.5
GPIO50: IC13.29, R385.1
GPIO51: IC13.31, R384.2, U78.6
GPIO52: GPIO13.1, IC13.21
GPIO53: IC14.27, R413.2, U84.5
GPIO54: IC14.29, R415.1
GPIO55: IC14.31, R414.2, U84.6
GPIO56: GPIO14.1, IC14.21
GPIO57: IC15.27, R443.2, U90.5
GPIO58: IC15.29, R445.1
GPIO59: IC15.31, R444.2, U90.6
GPIO60: GPIO15.1, IC15.21
MICROSD_CLK/SCK: J2.5, U3.12, U4.10, U5.9
MICROSD_CLK/SCK1: J6.5, U7.12, U8.10, U9.9
MICROSD_CLK/SCK2: J10.5, U13.12, U14.10, U15.9
MICROSD_CLK/SCK3: J14.5, U19.12, U20.10, U21.9
MICROSD_CLK/SCK4: J18.5, U25.12, U26.10, U27.9
MICROSD_CLK/SCK5: J22.5, U31.12, U32.10, U33.9
MICROSD_CLK/SCK6: J26.5, U37.12, U38.10, U39.9
MICROSD_CLK/SCK7: J30.5, U43.12, U44.10, U45.9
MICROSD_CLK/SCK8: J34.5, U49.12, U50.10, U51.9
MICROSD_CLK/SCK9: J38.5, U55.12, U56.10, U57.9
MICROSD_CLK/SCK10: J42.5, U61.12, U62.10, U63.9
MICROSD_CLK/SCK11: J46.5, U67.12, U68.10, U69.9
MICROSD_CLK/SCK12: J50.5, U73.12, U74.10, U75.9
MICROSD_CLK/SCK13: J54.5, U79.12, U80.10, U81.9
MICROSD_CLK/SCK14: J58.5, U85.12, U86.10, U87.9
MICROSD_CMD/SDI: J2.3, U4.9, U5.3
MICROSD_CMD/SDI1: J6.3, U8.9, U9.3
MICROSD_CMD/SDI2: J10.3, U14.9, U15.3
MICROSD_CMD/SDI3: J14.3, U20.9, U21.3
MICROSD_CMD/SDI4: J18.3, U26.9, U27.3
MICROSD_CMD/SDI5: J22.3, U32.9, U33.3
MICROSD_CMD/SDI6: J26.3, U38.9, U39.3
MICROSD_CMD/SDI7: J30.3, U44.9, U45.3
MICROSD_CMD/SDI8: J34.3, U50.9, U51.3
MICROSD_CMD/SDI9: J38.3, U56.9, U57.3
MICROSD_CMD/SDI10: J42.3, U62.9, U63.3
MICROSD_CMD/SDI11: J46.3, U68.9, U69.3
MICROSD_CMD/SDI12: J50.3, U74.9, U75.3
MICROSD_CMD/SDI13: J54.3, U80.9, U81.3
MICROSD_CMD/SDI14: J58.3, U86.9, U87.3
MICROSD_D0/SDO: J2.7, U4.2, U5.10
MICROSD_D0/SDO1: J6.7, U8.2, U9.10
MICROSD_D0/SDO2: J10.7, U14.2, U15.10
MICROSD_D0/SDO3: J14.7, U20.2, U21.10
MICROSD_D0/SDO4: J18.7, U26.2, U27.10
MICROSD_D0/SDO5: J22.7, U32.2, U33.10
MICROSD_D0/SDO6: J26.7, U38.2, U39.10
MICROSD_D0/SDO7: J30.7, U44.2, U45.10
MICROSD_D0/SDO8: J34.7, U50.2, U51.10
MICROSD_D0/SDO9: J38.7, U56.2, U57.10
MICROSD_D0/SDO10: J42.7, U62.2, U63.10
MICROSD_D0/SDO11: J46.7, U68.2, U69.10
MICROSD_D0/SDO12: J50.7, U74.2, U75.10
MICROSD_D0/SDO13: J54.7, U80.2, U81.10
MICROSD_D0/SDO14: J58.7, U86.2, U87.10
MICROSD_D1: J2.8, U5.2
MICROSD_D2: J2.1, U2.3
MICROSD_D3: J6.1, U11.3
MICROSD_D3/!CS!: J2.2, U2.2, U4.3
MICROSD_D3/!CS!1: J6.2, U8.3, U11.2
MICROSD_D3/!CS!2: J10.2, U14.3, U17.2
MICROSD_D3/!CS!3: J14.2, U20.3, U23.2
MICROSD_D3/!CS!4: J18.2, U26.3, U29.2
MICROSD_D3/!CS!5: J22.2, U32.3, U35.2
MICROSD_D3/!CS!6: J26.2, U38.3, U41.2
MICROSD_D3/!CS!7: J30.2, U44.3, U47.2
MICROSD_D3/!CS!8: J34.2, U50.3, U53.2
MICROSD_D3/!CS!9: J38.2, U56.3, U59.2
MICROSD_D3/!CS!10: J42.2, U62.3, U65.2
MICROSD_D3/!CS!11: J46.2, U68.3, U71.2
MICROSD_D3/!CS!12: J50.2, U74.3, U77.2
MICROSD_D3/!CS!13: J54.2, U80.3, U83.2
MICROSD_D3/!CS!14: J58.2, U86.3, U89.2
MICROSD_D4: J6.8, U9.2
MICROSD_D5: J10.1, U17.3
MICROSD_D6: J10.8, U15.2
MICROSD_D7: J14.1, U23.3
MICROSD_D8: J14.8, U21.2
MICROSD_D9: J18.1, U29.3
MICROSD_D10: J18.8, U27.2
MICROSD_D11: J22.1, U35.3
MICROSD_D12: J22.8, U33.2
MICROSD_D13: J26.1, U41.3
MICROSD_D14: J26.8, U39.2
MICROSD_D15: J30.1, U47.3
MICROSD_D16: J30.8, U45.2
MICROSD_D17: J34.1, U53.3
MICROSD_D18: J34.8, U51.2
MICROSD_D19: J38.1, U59.3
MICROSD_D20: J38.8, U57.2
MICROSD_D21: J42.1, U65.3
MICROSD_D22: J42.8, U63.2
MICROSD_D23: J46.1, U71.3
MICROSD_D24: J46.8, U69.2
MICROSD_D25: J50.1, U77.3
MICROSD_D26: J50.8, U75.2
MICROSD_D27: J54.1, U83.3
MICROSD_D28: J54.8, U81.2
MICROSD_D29: J58.1, U89.3
MICROSD_D30: J58.8, U87.2
MICROSD_PWR_EN: R26.1, U3.5
MICROSD_PWR_EN1: R56.1, U7.5
MICROSD_PWR_EN2: R86.1, U13.5
MICROSD_PWR_EN3: R116.1, U19.5
MICROSD_PWR_EN4: R146.1, U25.5
MICROSD_PWR_EN5: R176.1, U31.5
MICROSD_PWR_EN6: R206.1, U37.5
MICROSD_PWR_EN7: R236.1, U43.5
MICROSD_PWR_EN8: R266.1, U49.5
MICROSD_PWR_EN9: R296.1, U55.5
MICROSD_PWR_EN10: R326.1, U61.5
MICROSD_PWR_EN11: R356.1, U67.5
MICROSD_PWR_EN12: R386.1, U73.5
MICROSD_PWR_EN13: R416.1, U79.5
MICROSD_PWR_EN14: R446.1, U85.5
MICROSD_VCC: C5.1, J2.4, MICROSD_VCC.1, Q3.3
MICROSD_VCC1: C25.1, J6.4, MICROSD_VCC1.1, Q9.3
MICROSD_VCC2: C49.1, J10.4, MICROSD_VCC2.1, Q16.3
MICROSD_VCC3: C73.1, J14.4, MICROSD_VCC3.1, Q23.3
MICROSD_VCC4: C97.1, J18.4, MICROSD_VCC4.1, Q30.3
MICROSD_VCC5: C121.1, J22.4, MICROSD_VCC5.1, Q37.3
MICROSD_VCC6: C145.1, J26.4, MICROSD_VCC6.1, Q44.3
MICROSD_VCC7: C169.1, J30.4, MICROSD_VCC7.1, Q51.3
MICROSD_VCC8: C193.1, J34.4, MICROSD_VCC8.1, Q58.3
MICROSD_VCC9: C217.1, J38.4, MICROSD_VCC9.1, Q65.3
MICROSD_VCC10: C241.1, J42.4, MICROSD_VCC10.1, Q72.3
MICROSD_VCC11: C265.1, J46.4, MICROSD_VCC11.1, Q79.3
MICROSD_VCC12: C289.1, J50.4, MICROSD_VCC12.1, Q86.3
MICROSD_VCC13: C313.1, J54.4, MICROSD_VCC13.1, Q93.3
MICROSD_VCC14: C337.1, J58.4, MICROSD_VCC14.1, Q100.3
unnamed: J1.A5, R11.2
unnamed: J1.B5, R10.2
unnamed: C3.1, IC1.13
unnamed: C4.1, IC1.34
unnamed: Q5.2, Q5.5, Q5.6, R21.2
unnamed: Q3.1, R9.1, R26.2
unnamed: Q2.1, R20.2, R27.1
unnamed: Q2.3, R28.1
unnamed: J4.19, JP1.1
unnamed: J4.20, JP2.1
unnamed: J4.21, JP3.1
unnamed: J1.SHLD1, J1.SHLD2, J1.SHLD3, J1.SHLD4, SH.1
unnamed: Q4.1, Q5.3, R22.2
unnamed: I2C.3, R19.2
unnamed: Q7.2, Q7.5, Q7.6, R23.2
unnamed: I2C.1, R18.1
unnamed: Q1.1, R7.1, R28.2
unnamed: D2.A, R17.1
unnamed: D2.C, LED2.2
unnamed: IC1.30, R29.1
unnamed: J5.A5, R31.2
unnamed: D1.A, R8.1
unnamed: IC1.35, R16.2
unnamed: J5.B5, R32.2
unnamed: J4.14, RXD.1
unnamed: J4.15, TXD.1
unnamed: D1.C, LED1.2
unnamed: Q6.1, Q7.3, R24.2
unnamed: J8.19, JP5.1
unnamed: J8.20, JP6.1
unnamed: J8.21, JP7.1
unnamed: D4.A, R40.1
unnamed: D4.C, LED3.2
unnamed: D5.A, R43.1
unnamed: D5.C, LED4.2
unnamed: I2C1.3, R45.2
unnamed: I2C1.1, R44.1
unnamed: C29.1, IC2.13
unnamed: C30.1, IC2.34
unnamed: Q8.1, R38.1, R58.2
unnamed: IC2.35, R47.2
unnamed: J8.14, RXD1.1
unnamed: J8.15, TXD1.1
unnamed: Q12.2, Q12.5, Q12.6, R49.2
unnamed: Q11.1, Q12.3, R50.2
unnamed: Q14.2, Q14.5, Q14.6, R51.2
unnamed: Q13.1, Q14.3, R52.2
unnamed: Q9.1, R39.1, R56.2
unnamed: Q10.1, R46.2, R57.1
unnamed: Q10.3, R58.1
unnamed: J5.SHLD1, J5.SHLD2, J5.SHLD3, J5.SHLD4, SH1.1
unnamed: IC2.30, R59.1
unnamed: J9.A5, R61.2
unnamed: J9.B5, R62.2
unnamed: J12.19, JP9.1
unnamed: J12.20, JP10.1
unnamed: J12.21, JP11.1
unnamed: D7.A, R70.1
unnamed: D7.C, LED5.2
unnamed: D8.A, R73.1
unnamed: D8.C, LED6.2
unnamed: I2C2.3, R75.2
unnamed: I2C2.1, R74.1
unnamed: C53.1, IC3.13
unnamed: C54.1, IC3.34
unnamed: Q15.1, R68.1, R88.2
unnamed: IC3.35, R77.2
unnamed: J12.14, RXD2.1
unnamed: J12.15, TXD2.1
unnamed: Q19.2, Q19.5, Q19.6, R79.2
unnamed: Q18.1, Q19.3, R80.2
unnamed: Q21.2, Q21.5, Q21.6, R81.2
unnamed: Q20.1, Q21.3, R82.2
unnamed: Q16.1, R69.1, R86.2
unnamed: Q17.1, R76.2, R87.1
unnamed: Q17.3, R88.1
unnamed: J9.SHLD1, J9.SHLD2, J9.SHLD3, J9.SHLD4, SH2.1
unnamed: IC3.30, R89.1
unnamed: J13.A5, R91.2
unnamed: J13.B5, R92.2
unnamed: J16.19, JP13.1
unnamed: J16.20, JP14.1
unnamed: J16.21, JP15.1
unnamed: D10.A, R100.1
unnamed: D10.C, LED7.2
unnamed: D11.A, R103.1
unnamed: D11.C, LED8.2
unnamed: I2C3.3, R105.2
unnamed: I2C3.1, R104.1
unnamed: C77.1, IC4.13
unnamed: C78.1, IC4.34
unnamed: Q22.1, R98.1, R118.2
unnamed: IC4.35, R107.2
unnamed: J16.14, RXD3.1
unnamed: J16.15, TXD3.1
unnamed: Q26.2, Q26.5, Q26.6, R109.2
unnamed: Q25.1, Q26.3, R110.2
unnamed: Q28.2, Q28.5, Q28.6, R111.2
unnamed: Q27.1, Q28.3, R112.2
unnamed: Q23.1, R99.1, R116.2
unnamed: Q24.1, R106.2, R117.1
unnamed: Q24.3, R118.1
unnamed: J13.SHLD1, J13.SHLD2, J13.SHLD3, J13.SHLD4, SH3.1
unnamed: IC4.30, R119.1
unnamed: J17.A5, R121.2
unnamed: J17.B5, R122.2
unnamed: J20.19, JP17.1
unnamed: J20.20, JP18.1
unnamed: J20.21, JP19.1
unnamed: D13.A, R130.1
unnamed: D13.C, LED9.2
unnamed: D14.A, R133.1
unnamed: D14.C, LED10.2
unnamed: I2C4.3, R135.2
unnamed: I2C4.1, R134.1
unnamed: C101.1, IC5.13
unnamed: C102.1, IC5.34
unnamed: Q29.1, R128.1, R148.2
unnamed: IC5.35, R137.2
unnamed: J20.14, RXD4.1
unnamed: J20.15, TXD4.1
unnamed: Q33.2, Q33.5, Q33.6, R139.2
unnamed: Q32.1, Q33.3, R140.2
unnamed: Q35.2, Q35.5, Q35.6, R141.2
unnamed: Q34.1, Q35.3, R142.2
unnamed: Q30.1, R129.1, R146.2
unnamed: Q31.1, R136.2, R147.1
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
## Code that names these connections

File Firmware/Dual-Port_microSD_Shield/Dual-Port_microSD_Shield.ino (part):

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  D2:  Physical Pin 3  (PA2 / A2/RXD0)     : Serial RXD
  D3:  Physical Pin 2  (PA3 / A3)          : SDIO (USB2241) Enable
  D4:  Physical Pin 1  (PA4 / A4/SCK/SCL)  : I2C SCL
  D5:  Physical Pin 20 (PA5 / A5/CIPO)     : POCI - connected to pin 1 of the ISP header
  D6:  Physical Pin 16 (PA6 / A6/COPI/SDA) : I2C SDA
  D7:  Physical Pin 15 (PA7 / A7)          : Thing Plus 3V3 divided by 2
  D8:  Physical Pin 14 (PB2 / A8)          : USB 5V divided by 2
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//#define HEARTBEAT // Uncomment this line to output a heartbeat on serial

//Digital pins
const byte SPI_EN = 10; // SPI Enable: pull high to enable SPI buffer, pull low to disable
const byte MICROSD_CLK = 9; // MICROSD_CLK: could be used as an interrupt (INT0) to indicate SD card activity
const byte SDA_PIN = 6;
const byte SCL_PIN = 4;
const byte SDIO_EN = 3; // SDIO Enable: pull high to enable the USB2241 and its buffers, pull low to disable
const byte MICROSD_PWR_EN = 0; // microSD Power Enable: pull low to enable power for the microSD card, pull high or leave floating to disable

//Analog pins
const byte V_USB_DIV_2 = 8; // A8
const byte V_3V3_DIV_2 = 7; // A7

//Define the ON and OFF states for each pin
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
  // Disable the buffers, microSD card and the USB2241
  digitalWrite(SPI_EN, SPI_EN__OFF);
  pinMode(SPI_EN, OUTPUT);
  digitalWrite(SPI_EN, SPI_EN__OFF);
  
  digitalWrite(SDIO_EN, SDIO_EN__OFF);
  pinMode(SDIO_EN, OUTPUT);
  digitalWrite(SDIO_EN, SDIO_EN__OFF);

  digitalWrite(MICROSD_PWR_EN, MICROSD_PWR_EN__OFF);
  pinMode(MICROSD_PWR_EN, OUTPUT);
  digitalWrite(MICROSD_PWR_EN, MICROSD_PWR_EN__OFF);

#ifdef SERIAL_DIAGNOSTICS
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  digitalWrite(SPI_EN, SPI_EN__OFF); // Disable the SPI buffer
  delay(50);
  // Disable power for the microSD card
  pinMode(MICROSD_PWR_EN, INPUT_PULLUP); // Charge the FET Gate capacitance
  delay(10);
  digitalWrite(MICROSD_PWR_EN, MICROSD_PWR_EN__OFF); // Now drive the Gate high
  pinMode(MICROSD_PWR_EN, OUTPUT);
  digitalWrite(MICROSD_PWR_EN, MICROSD_PWR_EN__OFF);
  delay(40);
}
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
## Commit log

2021-12-21 Changed to 4-layer PCB. Routed. Add Schematic.pdf.
2021-12-22 Add silk. Replace xtal caps with calculated values. Finishing touches...
2021-12-23 Corrected 74HC4066 footprint. Swapped U4 and U5.
2021-12-23 Add firmware
2021-12-24 Add code examples
2021-12-24 Add footprint for optional I2C EEPROM
2022-01-20 Final Eagle files for Proto
2022-01-26 Updates post proto review
2022-01-27 Nudged the silk labels
2022-01-27 Add Gerbers
2022-03-03 Updates after testing proto
2022-03-04 Update firmware: clear the I2C event as early as possible, ready for the next
2022-03-04 Add v10 hardware files
2022-03-14 Updated hardware files after REDS Review
2022-03-16 Update firmware after REDS code review. Move examples to Arduino Library.
2022-05-09 Firmware v1.1
2022-05-10 PCB v1.1
